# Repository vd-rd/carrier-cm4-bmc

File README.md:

# Raspberry PI4 Compute Module Carrier Board

Based on the work of [@PTS93](https://github.com/PTS93)'s [awesome board](https://github.com/PTS93/Minimal-RPi-CM-4-Carrier).

## Description
The module is designed using Autodesk Eagle. It is meant to provide I/O, power and comms for the RPI CM4.
TBD

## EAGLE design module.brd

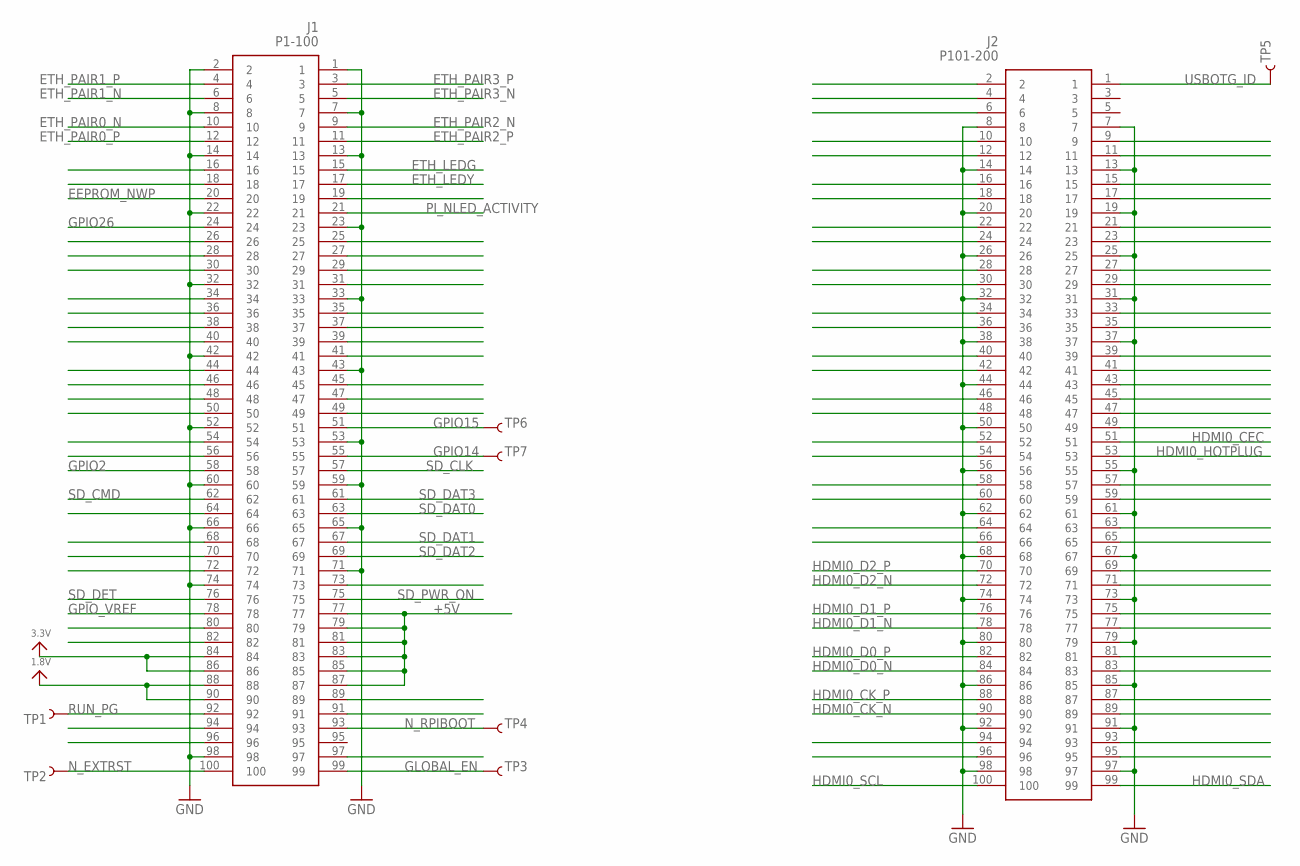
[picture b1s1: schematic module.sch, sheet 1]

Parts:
J1: P1-100; DF40C100DS04V51
J2: P101-200; DF40C100DS04V51
TP1, TP2, TP3, TP4, TP5, TP6, TP7: TEST-POINT3X5; PAD.03X.05

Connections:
1.8V: J1.88, J1.90
3.3V: J1.84, J1.86
+5V: J1.77, J1.79, J1.81, J1.83, J1.85, J1.87
EEPROM_NWP: J1.20
ETH_LEDG: J1.15
ETH_LEDY: J1.17
ETH_PAIR0_N: J1.10
ETH_PAIR0_P: J1.12
ETH_PAIR1_N: J1.6
ETH_PAIR1_P: J1.4
ETH_PAIR2_N: J1.9
ETH_PAIR2_P: J1.11
ETH_PAIR3_N: J1.5
ETH_PAIR3_P: J1.3
GLOBAL_EN: J1.99, TP3.P$1
GND: J1.1, J1.2, J1.7, J1.8, J1.13, J1.14, J1.22, J1.23, J1.32, J1.33, J1.42, J1.43, J1.52, J1.53, J1.59, J1.60, J1.65, J1.66, J1.71, J1.74, J1.98, J2.7, J2.8, J2.13, J2.14, J2.19, J2.20, J2.25, J2.26, J2.31, J2.32, J2.37, J2.38, J2.44, J2.50, J2.55, J2.56, J2.61, J2.62, J2.67, J2.68, J2.73, J2.74, J2.79, J2.80, J2.85, J2.86, J2.91, J2.92, J2.97, J2.98; also elsewhere on the board
GPIO2: J1.58
GPIO14: J1.55, TP7.P$1
GPIO15: J1.51, TP6.P$1
GPIO26: J1.24
GPIO_VREF: J1.78
HDMI0_CEC: J2.51
HDMI0_CK_N: J2.90
HDMI0_CK_P: J2.88
HDMI0_D0_N: J2.84
HDMI0_D0_P: J2.82
HDMI0_D1_N: J2.78
HDMI0_D1_P: J2.76
HDMI0_D2_N: J2.72
HDMI0_D2_P: J2.70
HDMI0_HOTPLUG: J2.53
HDMI0_SCL: J2.100
HDMI0_SDA: J2.99
N_EXTRST: J1.100, TP2.P$1
N_RPIBOOT: J1.93, TP4.P$1
PI_NLED_ACTIVITY: J1.21
RUN_PG: J1.92, TP1.P$1
SD_CLK: J1.57
SD_CMD: J1.62
SD_DAT0: J1.63
SD_DAT1: J1.67
SD_DAT2: J1.69
SD_DAT3: J1.61
SD_DET: J1.76
SD_PWR_ON: J1.75
USBOTG_ID: J2.1, TP5.P$1

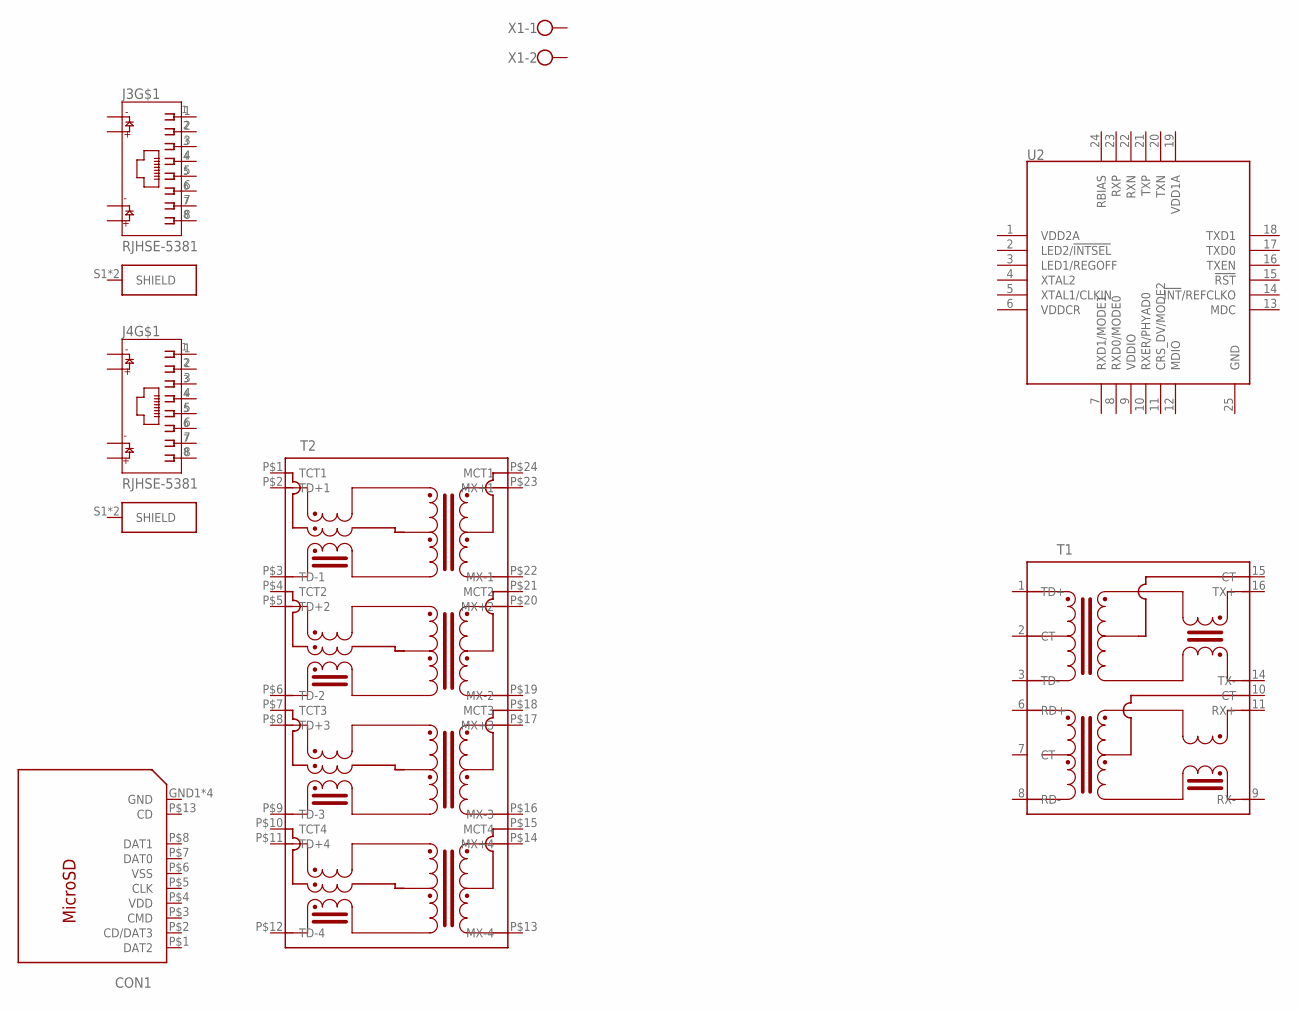
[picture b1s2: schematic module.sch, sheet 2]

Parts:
CON1: 112J-TXAR; 112J
J3, J4: RJHSE-5381; AMPHENOL_RJHSE-5381
T1: PT61017PEL; PT61017
T2: SM51625; SM61625EL
U2: LAN8720A; QFN50P400X400X100-25T250N
X1: W237-102; EBBA

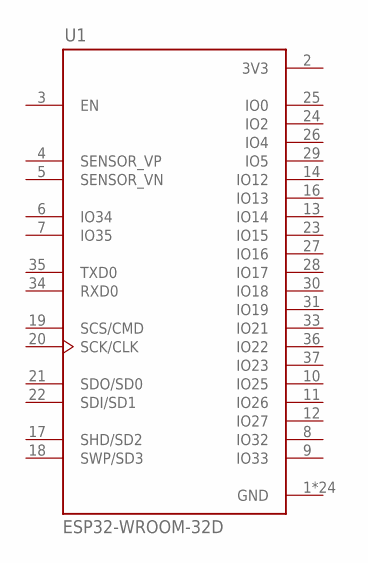
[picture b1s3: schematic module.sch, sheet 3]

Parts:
U1: ESP32-WROOM-32D; MODULE_ESP32-WROOM-32D

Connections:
3V3: U1.2 (3V3)
GND: U1.1 (GND), U1.15 (GND), U1.38 (GND), U1.39_1 (GND), U1.39_2 (GND), U1.39_3 (GND), U1.39_4 (GND), U1.39_5 (GND), U1.39_6 (GND), U1.39_7 (GND), U1.39_8 (GND), U1.39_9 (GND), U1.39_10 (GND), U1.39_11 (GND), U1.39_12 (GND), U1.39_13 (GND), U1.39_14 (GND), U1.39_15 (GND), U1.39_16 (GND), U1.39_17 (GND), U1.39_18 (GND), U1.39_19 (GND), U1.39_20 (GND), U1.39_21 (GND); also elsewhere on the board

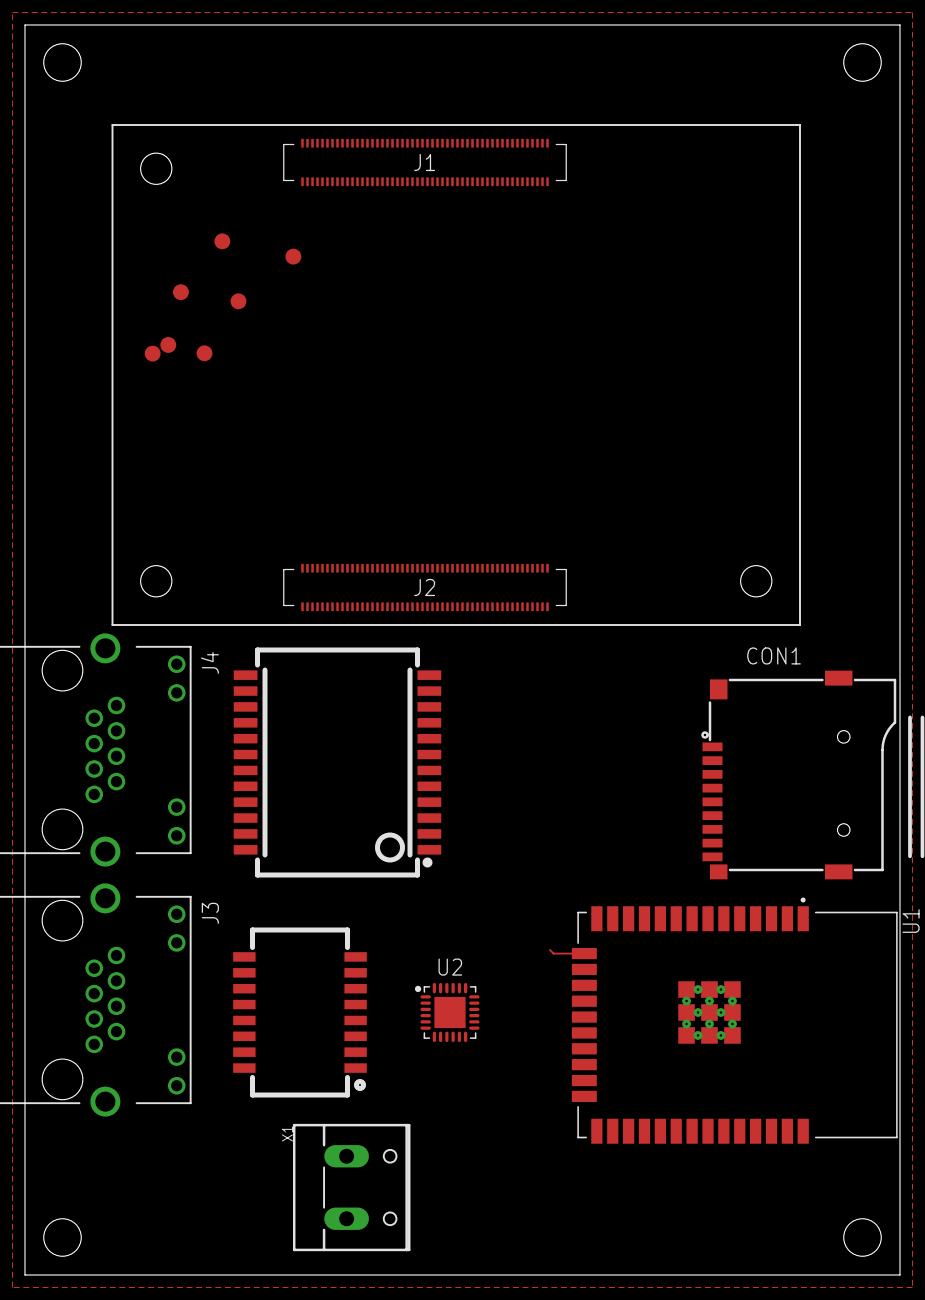
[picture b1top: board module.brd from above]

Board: 2 copper layers, 70.0 x 100.0 mm, 17 parts (0 on the bottom side), 11 nets.

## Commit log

2020-12-02 project: initial board bringup
2020-12-02 project: adjusted drc and added main components
2020-12-02 schematic: rename connector nets

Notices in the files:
parts and their libraries:
SparkFun-Connectors: Licensing: Creative Commons ShareAlike 4.0 International - https://creativecommons.org/licenses/by-sa/4.0
microbuilder: This work is placed in the public domain, and may be freely used for commercial and non-commercial work with the following conditions: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
